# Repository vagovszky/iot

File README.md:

# IoT project
IoT project with usage of ESP8266 - [Wiki page](https://github.com/vagovszky/iot/wiki)

## Roadmapa - sketch

### Hardware - Hlavní modul

- [X] Návrh HW - schema (únor 2017)
- [X] Návrh HW - DPS (únor 2017)
- [X] Výroba DPS - Prototyp (únor 2017)
- [X] Osazení DPS (brezen 2017)
- [X] Celková kompletace modulu (brezen 2017)
- [X] Základní otestování (brezen 2017)

### Hardware - Přídavné moduly

- [X] Modul čidlo teploty
- [X] Modul I/O

## Výsledná sestava

## Screenshot z webové aplikace k ovládání modulu

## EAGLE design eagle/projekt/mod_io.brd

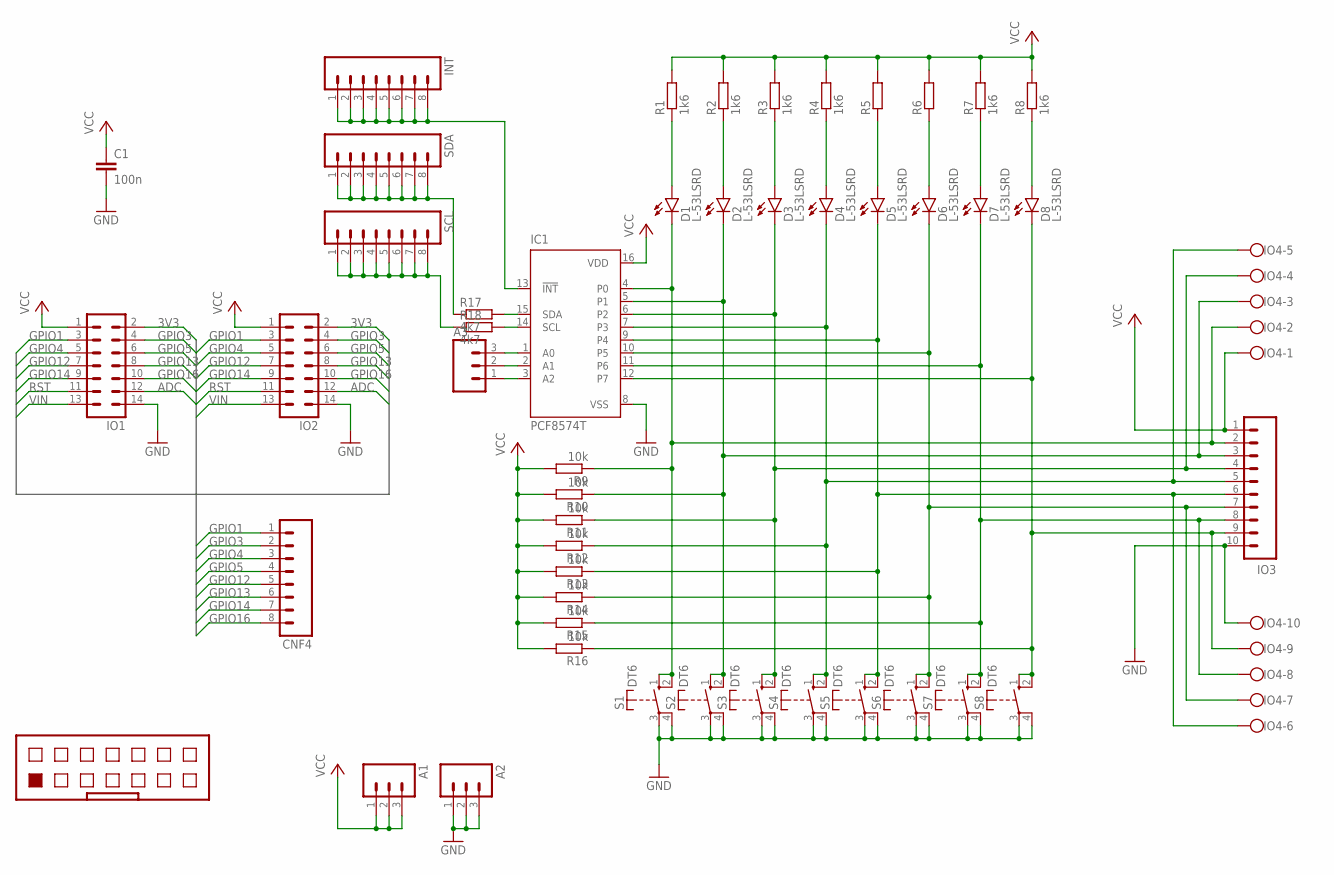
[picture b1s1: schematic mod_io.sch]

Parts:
A1, A2, A3: M03LONGPADS; 1X03_LONGPADS
C1: 100n; C050-025X075
CNF4: M08LONGPADS; 1X08_LONGPADS
D1, D2, D3, D4, D5, D6, D7, D8: L-53LSRD; LED5MM
IC1: PCF8574T; SO16W
INT: M08LONGPADS; 1X08_LONGPADS
IO1, IO2: 14V
IO3: M10LOCK_LONGPADS; 1X10_LOCK_LONGPADS
IO4: AK550/10
R1, R2, R3, R4, R7, R8: 1k6; 0207/10
R5, R6: R-EU_0207/10; 0207/10
R9, R10, R11, R12, R13, R14, R15, R16: 10k; 0207/10
R17, R18: 4k7; 0207/10
S1, S2, S3, S4, S5, S6, S7, S8: DT6
SCL: M08LONGPADS; 1X08_LONGPADS
SDA: M08LONGPADS; 1X08_LONGPADS

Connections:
3V3: IO1.2, IO2.2
ADC: IO1.12, IO2.12
GND: A2.1, A2.2, A2.3, C1.2, IC1.8 (VSS), IO1.14, IO2.14, IO3.10, IO4.10, S1.3, S1.4, S2.3, S2.4, S3.3, S3.4, S4.3, S4.4, S5.3, S5.4, S6.3, S6.4, S7.3, S7.4, S8.3, S8.4
GPIO1: CNF4.1, IO1.3, IO2.3; also elsewhere on the board
GPIO3: CNF4.2, IO1.4, IO2.4; also elsewhere on the board
GPIO4: CNF4.3, IO1.5, IO2.5; also elsewhere on the board
GPIO5: CNF4.4, IO1.6, IO2.6; also elsewhere on the board
GPIO12: CNF4.5, IO1.7, IO2.7; also elsewhere on the board
GPIO13: CNF4.6, IO1.8, IO2.8; also elsewhere on the board
GPIO14: CNF4.7, IO1.9, IO2.9; also elsewhere on the board
GPIO16: CNF4.8, IO1.10, IO2.10; also elsewhere on the board
unnamed: D5.K (C), IC1.9 (P4), IO3.6, IO4.6, R13.1, S5.1 (S), S5.2 (S)
unnamed: D6.K (C), IC1.10 (P5), IO3.7, IO4.7, R14.1, S6.1 (S), S6.2 (S)
unnamed: D1.K (C), IC1.4 (P0), IO3.2, IO4.2, R9.1, S1.1 (S), S1.2 (S)
unnamed: D2.K (C), IC1.5 (P1), IO3.3, IO4.3, R10.1, S2.1 (S), S2.2 (S)
unnamed: D3.K (C), IC1.6 (P2), IO3.4, IO4.4, R11.1, S3.1 (S), S3.2 (S)
unnamed: D4.K (C), IC1.7 (P3), IO3.5, IO4.5, R12.1, S4.1 (S), S4.2 (S)
unnamed: D7.K (C), IC1.11 (P6), IO3.8, IO4.8, R15.1, S7.1 (S), S7.2 (S)
unnamed: D8.K (C), IC1.12 (P7), IO3.9, IO4.9, R16.1, S8.1 (S), S8.2 (S)
unnamed: D6.A, R6.1
unnamed: D5.A, R5.1
unnamed: D7.A, R7.1
unnamed: D8.A, R8.1
unnamed: D1.A, R1.1
unnamed: D2.A, R2.1
unnamed: D3.A, R3.1
unnamed: D4.A, R4.1
unnamed: IC1.13 (!INT), INT.1, INT.2, INT.3, INT.4, INT.5, INT.6, INT.7, INT.8
unnamed: A3.3, IC1.1 (A0)
unnamed: A3.2, IC1.2 (A1)
unnamed: A3.1, IC1.3 (A2)
unnamed: IC1.15 (SDA), R17.2
unnamed: IC1.14 (SCL), R18.2
unnamed: R17.1, SDA.1, SDA.2, SDA.3, SDA.4, SDA.5, SDA.6, SDA.7, SDA.8
unnamed: R18.1, SCL.1, SCL.2, SCL.3, SCL.4, SCL.5, SCL.6, SCL.7, SCL.8
RST: IO1.11, IO2.11
VCC: A1.1, A1.2, A1.3, C1.1, IC1.16 (VDD), IO1.1, IO2.1, IO3.1, IO4.1, R1.2, R2.2, R3.2, R4.2, R5.2, R6.2, R7.2, R8.2, R9.2, R10.2, R11.2, R12.2, R13.2, R14.2, R15.2, R16.2
VIN: IO1.13, IO2.13

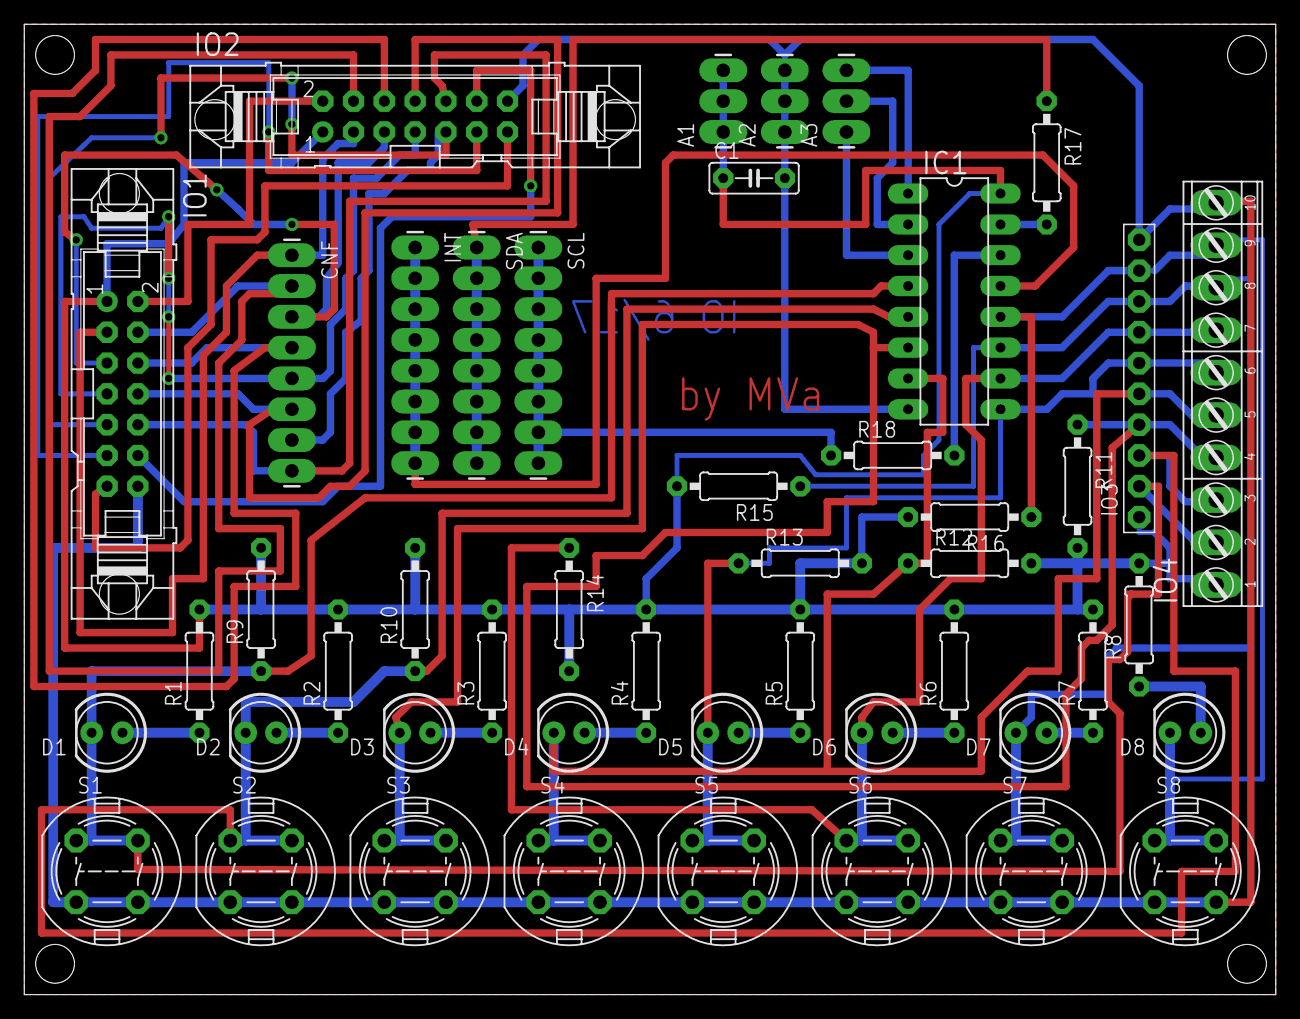
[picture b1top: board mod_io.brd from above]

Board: 2 copper layers, 103.2 x 80.0 mm, 47 parts (0 on the bottom side), 38 nets.

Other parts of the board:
CNF: 1X08_LONGPADS

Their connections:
GPIO1: CNF.1; also elsewhere on the board
GPIO3: CNF.2; also elsewhere on the board
GPIO4: CNF.3; also elsewhere on the board
GPIO5: CNF.4; also elsewhere on the board
GPIO12: CNF.5; also elsewhere on the board
GPIO13: CNF.6; also elsewhere on the board
GPIO14: CNF.7; also elsewhere on the board
GPIO16: CNF.8; also elsewhere on the board

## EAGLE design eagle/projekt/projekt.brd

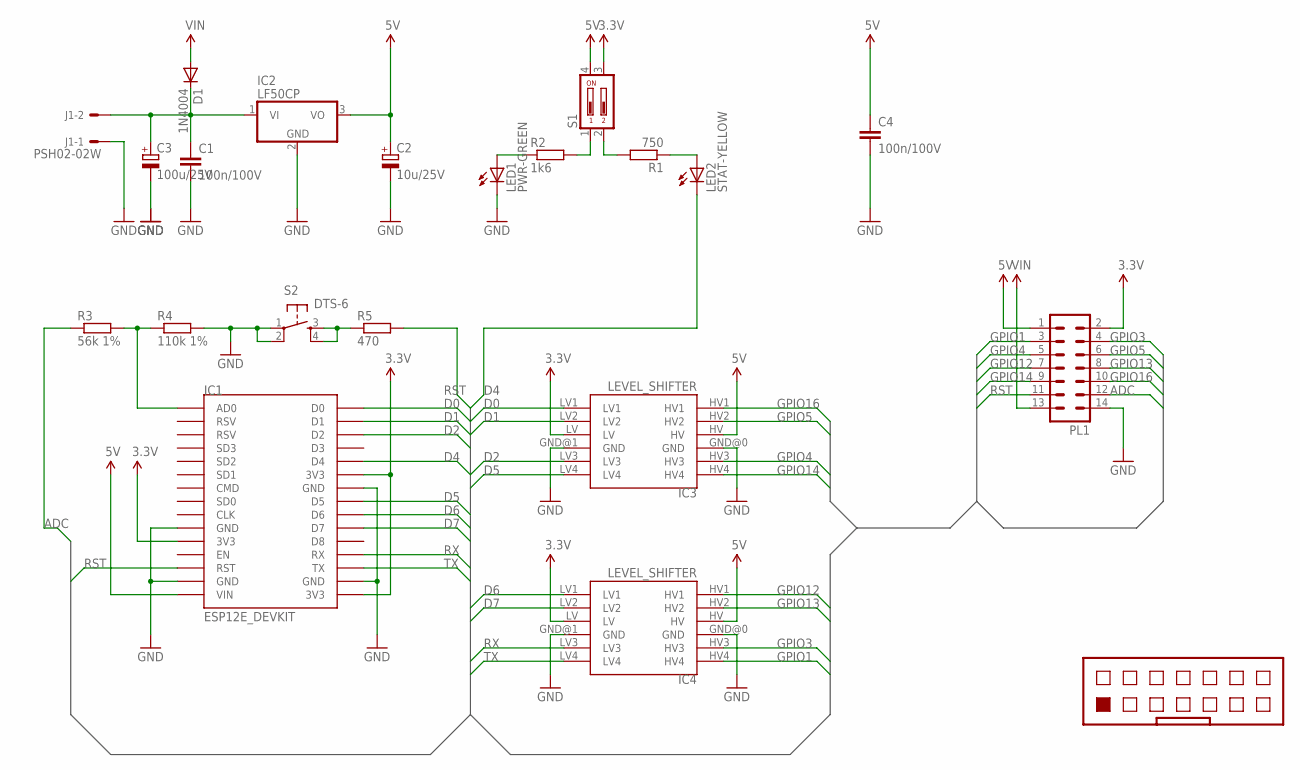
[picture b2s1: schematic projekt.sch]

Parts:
C1, C4: 100n/100V; C025-025X050
C2: 10u/25V; E3,5-8
C3: 100u/25V; E5-13
D1: 1N4004; DO41-10
IC1: ESP12E_DEVKIT
IC2: LF50CP; TO220H
IC3, IC4: LEVEL_SHIFTER
J1: PSH02-02W; 7395-02
LED1: PWR-GREEN; LED3MM
LED2: STAT-YELLOW; LED3MM
PL1: 14H
R1: 750; R1206
R2: 1k6; R1206
R3: 56k 1%; R1206
R4: 110k 1%; R1206
R5: 470; R1206
S1: DIP02YL
S2: DTS-6

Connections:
3.3V: IC1.3V3@0 (3V3), IC1.3V3@1 (3V3), IC1.3V3@2 (3V3), IC3.LV, IC4.LV, PL1.2, S1.3
5V: C2.+, C4.1, IC1.VIN, IC2.3 (VO), IC3.HV, IC4.HV, PL1.1, S1.4
ADC: PL1.12, R3.1
D0: IC1.D0, IC3.LV1
D1: IC1.D1, IC3.LV2
D2: IC1.D2, IC3.LV3
D4: IC1.D4, LED2.K (C)
D5: IC1.D5, IC3.LV4
D6: IC1.D6, IC4.LV1
D7: IC1.D7, IC4.LV2
GND: C1.2, C2.-, C3.-, C4.2, IC1.GND@0 (GND), IC1.GND@1 (GND), IC1.GND@2 (GND), IC1.GND@3 (GND), IC2.2 (GND), IC3.GND@0 (GND), IC3.GND@1 (GND), IC4.GND@0 (GND), IC4.GND@1 (GND), J1.1, LED1.K (C), PL1.14, R4.2, S2.1, S2.2
GPIO1: IC4.HV4, PL1.3
GPIO3: IC4.HV3, PL1.4
GPIO4: IC3.HV3, PL1.5
GPIO5: IC3.HV2, PL1.6
GPIO12: IC4.HV1, PL1.7
GPIO13: IC4.HV2, PL1.8
GPIO14: IC3.HV4, PL1.9
GPIO16: IC3.HV1, PL1.10
unnamed: IC1.AD0, R3.2, R4.1
unnamed: LED1.A, R2.1
unnamed: R2.2, S1.1
unnamed: R5.1, S2.3, S2.4
unnamed: R1.2, S1.2
unnamed: LED2.A, R1.1
unnamed: C1.1, C3.+, D1.C, IC2.1 (VI), J1.2
RST: IC1.RST, PL1.11, R5.2
RX: IC1.RX, IC4.LV3
TX: IC1.TX, IC4.LV4
VIN: D1.A, PL1.13

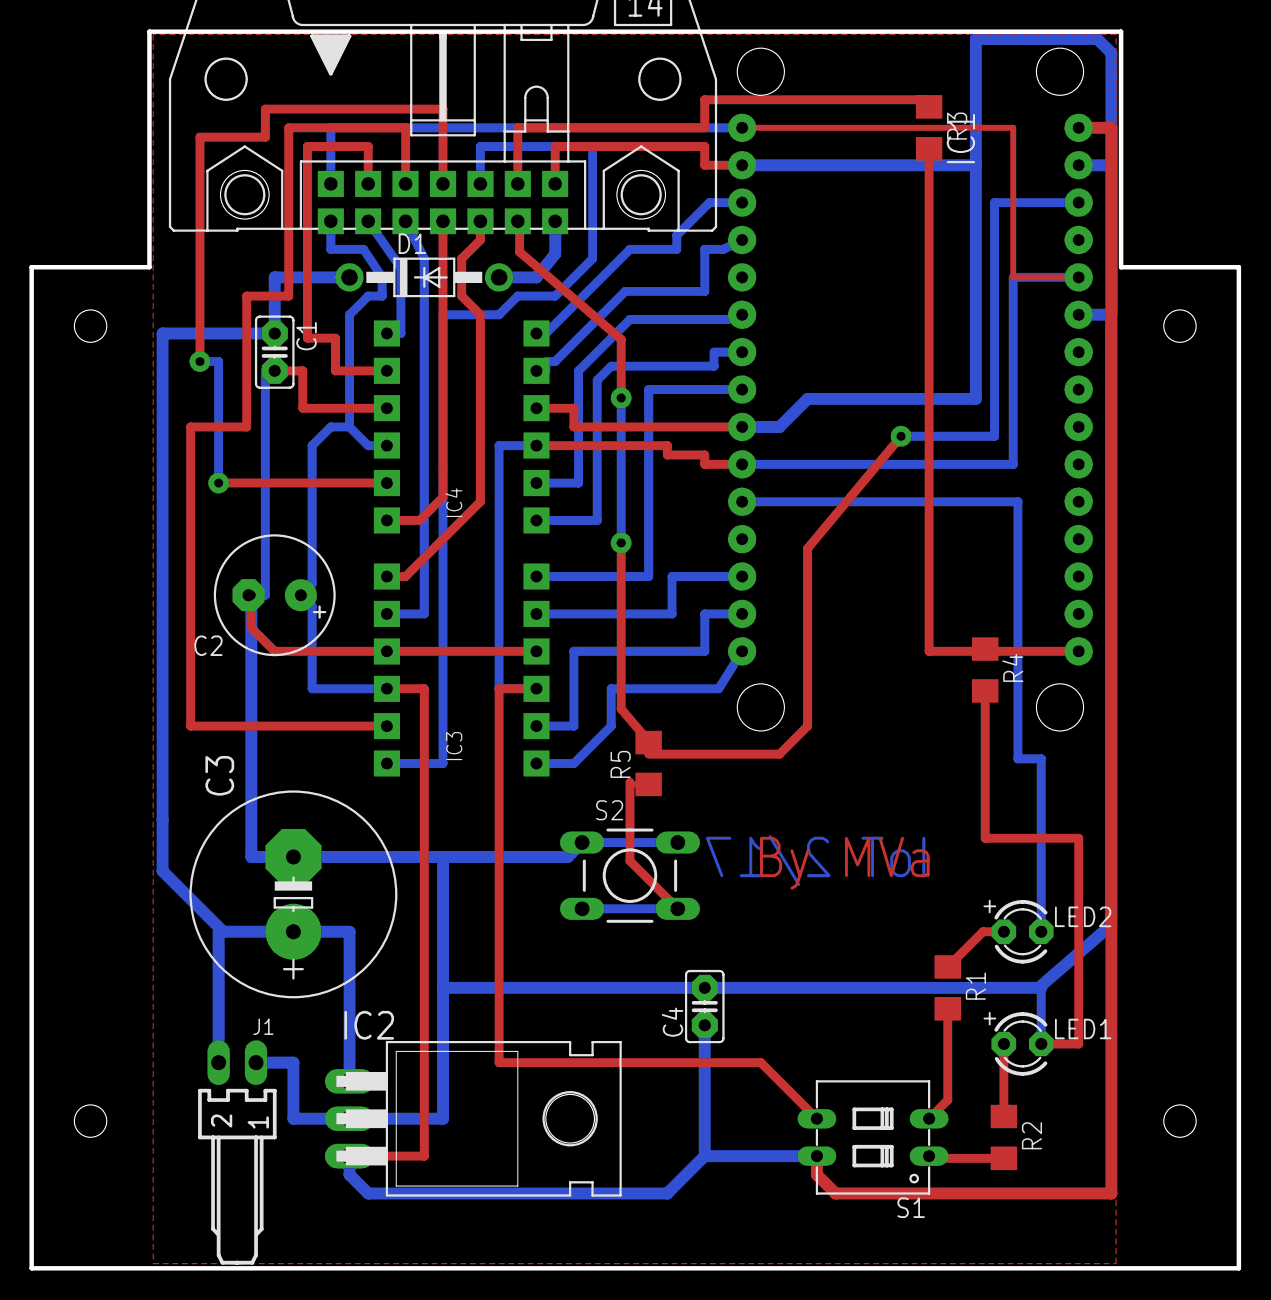
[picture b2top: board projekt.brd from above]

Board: 2 copper layers, 82.0 x 84.0 mm, 20 parts (0 on the bottom side), 30 nets.

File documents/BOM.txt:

C1,C4 KONDENZATOR 100n/100V - 2ks                      
C2    KONDENZATOR 10u/25V ELYT - 1ks                  
C3    KONDENZATOR 100u/25V ELYT - 1ks                 
D1    DIODA 1N4004 - 1ks                     
IC1   ESP12E_DEVKIT (EBAY) - 0ks       
IC2   REGULATOR LF50CP TO220H 5V LDO Regulator - 1ks          
IC3   LEVEL_SHIFTER Level shifter 5V <-> 3.3V (EBAY) - 0ks    
IC4   LEVEL_SHIFTER Level shifter 5V <-> 3.3V (EBAY) - 0ks   
J1    KONEKTOR PSH02-02W + OPACNÝ DÍL + PINY - 1ks                
LED1  LED 3MM Green BL-B2141-L (1,8V / 2mA) - 1ks                      
LED2  LED 3MM YELLOW HLMP-1719 (1,8V / 2mA) - 1ks                       
PL1   KONEKTOR PSL14W - 1ks                 
R1    REZISTOR 750 SMD 1206 - 2ks 
R2    REZISTOR 1k6 SMD 1206 - 2ks 
R3    REZISTOR 56k 1% SMD 1206 - 2ks 
R4    REZISTOR 110k 1% SMD 1206 - 2ks 
R5    REZISTOR 470 SMD 1206 - 2ks 
S1    SPÍNAC DO DPS DIP 02 RED/BLACK - 1ks          
S2    MIKROSPINAC DO DPS (asi TC-0111-T 13.5MM) - zmmerit delku hmatniku - 1ks
S3    POSUVNY SPINAC JEDNOPOLOVY CERNY DO PANELU - 1ks

Objímka pro led 3mm do panelu (reflektor / sokl) - 2ks
KONEKTOR PFL14 (NA KABEL) + TRMEN - 4ks
Podloky pod sroub M3 plastove
Distancni sloupek plastovy maly (5mm)

Krabicka H-75/4AA - 0ks
Plochý kabel - 14 il - 1m

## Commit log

2017-02-08 Roadmapa
2017-02-08 Pridani obrazku Nodemcu mapa pinu
2017-02-08 Pridan odkaz na wiki stranku
2017-02-09 Aktualizace obrazku, BOM, uctenka krabicka
2017-02-09 Aktualizace BOM, datasheet LDO reg.
2017-02-10 Eagle - schema, knihovny
2017-02-12 Schema
2017-02-13 ESP12E interni schema.
2017-02-16 Board
2017-02-17 Podklady pro vyrobu DPS
2017-02-20 Board - podklady
2017-02-20 Readme update
2017-02-21 Osazovak
2017-02-21 Partlist
2017-02-24 Fotka vyrobene desky
2017-03-06 Seznam soucastek
2017-03-07 Seznam soucastek update
2017-03-12 Nakres predniho panelu
2017-03-22 Osazena deska + label
2017-03-23 Potisk
2017-03-24 Stitek
2017-04-02 Datasheet ESP8266
2017-04-12 Schema - Rev 2
2017-04-12 Mod temp
2017-04-16 Cidlo teploty
2017-04-16 Readme
2017-04-16 Odkazy
2017-05-04 Added document
2017-05-26 Fotky
2017-05-31 Lua kod/priklady
2017-05-31 Update schematu
2017-06-01 Deska mod IO
2017-06-01 Deska, modul IO
2017-06-02 Modul IO deska podklady
2017-10-10 Frontend
2017-10-11 Pridani registru do vracenych hodnot
2017-10-11 Init.lua
2017-10-11 Aplikace - update
2017-10-11 Uprava v kodu
2017-10-11 Upravy - JS
2017-10-11 Zaukrouhleni teploty a vlhkosti na 1 des. misto
2017-10-12 Uprava vzhledu
2017-10-13 Ladeni frontendu
2017-10-16 Zjednodusseni aplikace
2017-10-16 Odmazani nepotrebnych radku
2017-10-27 Disable - pokud neni pripojeno
2017-10-31 Bliknuti ledkou pri prijeti nebo odeslani zpravy
2017-12-14 Update obrazku
2017-12-14 Pridany obrazky
2017-12-19 Obrazek aplikace
2018-02-26 Robot.html
2018-02-27 Robot Controller
2018-03-04 Robot.html - update
2018-03-27 Add menu item
2018-05-04 README update, predni stitek - PDF

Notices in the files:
parts and their libraries:
SparkFun-Connectors: Licensing: Creative Commons ShareAlike 4.0 International - https://creativecommons.org/licenses/by-sa/4.0
